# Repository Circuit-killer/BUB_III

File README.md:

# BUB_III
Eagle files and docs for the BUB III

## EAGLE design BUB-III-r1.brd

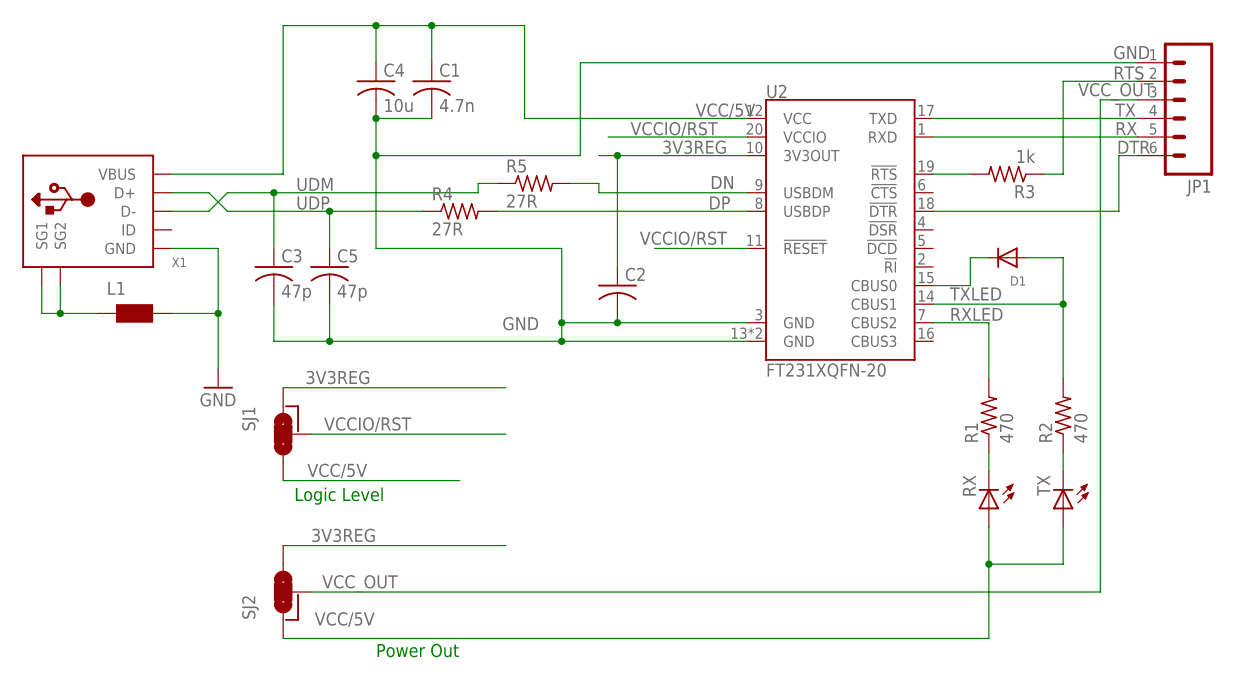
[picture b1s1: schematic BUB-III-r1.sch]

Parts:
C1: 4.7n; C0603K
C2: C-USC0603K; C0603K
C3, C5: 47p; C0603K
C4: 10u; C0805K
D1: DIODE_SOD-323; SOD-323
JP1: M06SMD-FEMALE-V2; 1X06-SMD-FEMALE-V2
L1: FERRITE_BEAD_0603; WUERTH-ELEKTRONIK_0603
R1, R2: 470; R0603
R3: 1k; R0603
R4, R5: 27R; R0603
RX: LEDCHIP-LED0805; CHIP-LED0805
SJ1, SJ2: SOLDERJUMP_SPDTSHORT_PASTE; SJ-SHRTINPASTE
TX: LEDCHIP-LED0805; CHIP-LED0805
U2: FT231XQFN-20; QFN-20
X1: USB; USB-AB-MICRO-SMD

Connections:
3V3REG: C2.1, SJ1.1, SJ2.3, U2.10 (3V3OUT)
DN: R5.2, U2.9 (USBDM)
DP: R4.2, U2.8 (USBDP)
DTR: JP1.6, U2.18 (!DTR)
GND: C1.2, C2.2, C3.2, C4.2, C5.2, JP1.1, L1.2, U2.3 (GND), U2.13 (GND), U2.P (GND), X1.GND
unnamed: D1.C, U2.15 (CBUS0)
unnamed: R1.1, RX.C
unnamed: R2.1, TX.C
unnamed: R3.2, U2.19 (!RTS)
RTS: JP1.2, R3.1
RX: JP1.5, U2.1 (RXD)
RXLED: R1.2, U2.7 (CBUS2)
TX: JP1.4, U2.17 (TXD)
TXLED: D1.A, R2.2, U2.14 (CBUS1)
UDM: C3.1, R5.1, X1.D-
UDP: C5.1, R4.1, X1.D+
USB_CASE: L1.1, X1.P$1 (SG1), X1.P$2 (SG2), X1.P$3 (SG1), X1.P$4 (SG2)
VCC/5V: C1.1, C4.1, RX.A, SJ1.3, SJ2.1, TX.A, U2.12 (VCC), X1.VBUS
VCCIO/RST: SJ1.2, U2.11 (!RESET), U2.20 (VCCIO)
VCC_OUT: JP1.3, SJ2.2

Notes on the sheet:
Power Out
Logic Level

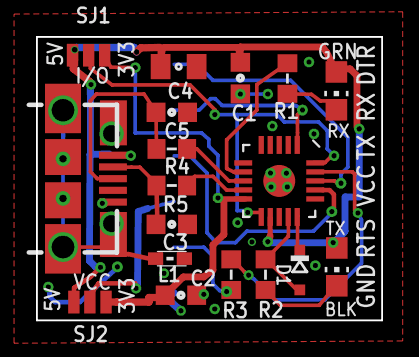
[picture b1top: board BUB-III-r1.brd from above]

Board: 2 copper layers, 19.2 x 15.7 mm, 19 parts (1 on the bottom side), 20 nets.

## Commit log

2015-11-10 Added PDF of schematic
